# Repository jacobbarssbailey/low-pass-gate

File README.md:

# Dual low pass gate

This project provides tested plans for a 8HP Eurorack-format Dual Low Pass Gate.

## BOM

| Qty | Device | Value | Package | Parts | Notes |
| --- | ------ | ----- | ------- | ----- | ----- |
| 8 | Resistor | 1K | 0603 | R7, R11, R15, R24, R28, R32 | |
| 2 | Resistor | 4.7K | 0603 | R9, R27 | |
| 4 | Resistor | 47K | 0603 | R13, R17, R30, R34 | |
| 4 | Resistor | 10K | 0603 | R4, R14, R20, R31 | |
| 4 | Resistor | 100K | 0603 | R8, R16, R25, R33 | |
| 12 | Resistor | 200K | 0603 | R1, R2, R3, R5, R10, R12, R18, R19, R21, R22, R26, R29 | |
| 2 | Capacitor | 100p | 0603 | C3, C12 | |
| 2 | Capacitor | 560p | 0603 | C21, C22 | |
| 2 | Capacitor | 1.5n | 0603 | C4, C13 | |
| 8 | Capacitor | 100n | 0603 | C1, C5, C6, C8, C10, C15, C16, C19 | |
| 2 | Capacitor | 1µ | 0603 | C2, C11 | |
| 2 | Capacitor (Pol) | 47µ–100µ | Panasonic D | C14, C18 | |
| 4 | Pot | 100K | ALPS 9mm Vert | GAIN1, GAIN2, RMUTE1, RMUTE2 | |
| 10 | Audio Jack (Mono) |  | Inline | CTRL1, CTRL2, IN1, IN2, MUTE1, MUTE2, OUT1, OUT2, PLK1, PLK2 | [Erthenvar](https://erthenvar.myshopify.com/collections/accessories/products/3-5mm-inline-jacks) and others |
| 2 | Quad Op Amp | TL074 | SO14 | U1, U2 |  |
| 2 | Comparator | LM397 | SOT23-5 | IC2, IC5 |  |
| 8 | Schottky Diode |  | SOD323 | D1, D2, D3, D4, D5, D6, D7, D8 |  |
| 6 | Light Dependent Resistor | SR32-SR3 | VTL5C-SMALL | LDR1, LDR2, LDR3, LDR4, LDR5, LDR6 | [digikey.com](https://www.digikey.com/product-detail/en/advanced-photonix/NSL-32SR3/NSL-32SR3-ND/5039793) and others |
| 1 | 10 pin Power |  | 10 pin shrouded IDC 2.54mm pitch | P1 |  |
| 2 | LED[†](#leds) |  | 3mm | LED1, LED2 |  |

#### †LEDs
In the drive circuit, indicator LEDs and LDRs are driven in series, with identical current. For best results, use LEDs that have a acceptable brightness when driven in the range 0mA – 12mA.

### Assembly [important!]

The pairs of jacks IN1 & CTRL1 and IN2 & CTRL2 share a ground pin connection. Make sure to check CTRL1 and CTRL2 orientation before soldering.

## Operation and Controls

Each channel of the gate/filter is identical, save that Channel B's Audio Input is normalled to Channel A's.

 The control knob opens the filter and allows audio to pass. It attenuates the Control CV (normalled to =6V).

Pluck CV is a gate-to-trigger converter feeding the control circuit. Gate signals sent to this input will 'pluck' the control circuit, causing it to ring out.

 The mute input (normalled to =10V) will both shorten the response time of the filter, and apply a very mild hi-pass filter. In a musical sense, its effect on the filter is akin to softly holding a palm against a rung bell or plucked string.

 At very low values, near 0V the mute input will allow some audio to pass through the circuit without any control input. If this isn't desired, turn the mute knob up to 15-20%.

## Other notes

Increasing the capacitance of C21 and C22 will increase the resonance of the low pass filter. Quite strong filter resonance is achievable by changing this component value.

Other LDRs/Vactrols may work equally well. If test any and have particular recommendations, please open an issue here.

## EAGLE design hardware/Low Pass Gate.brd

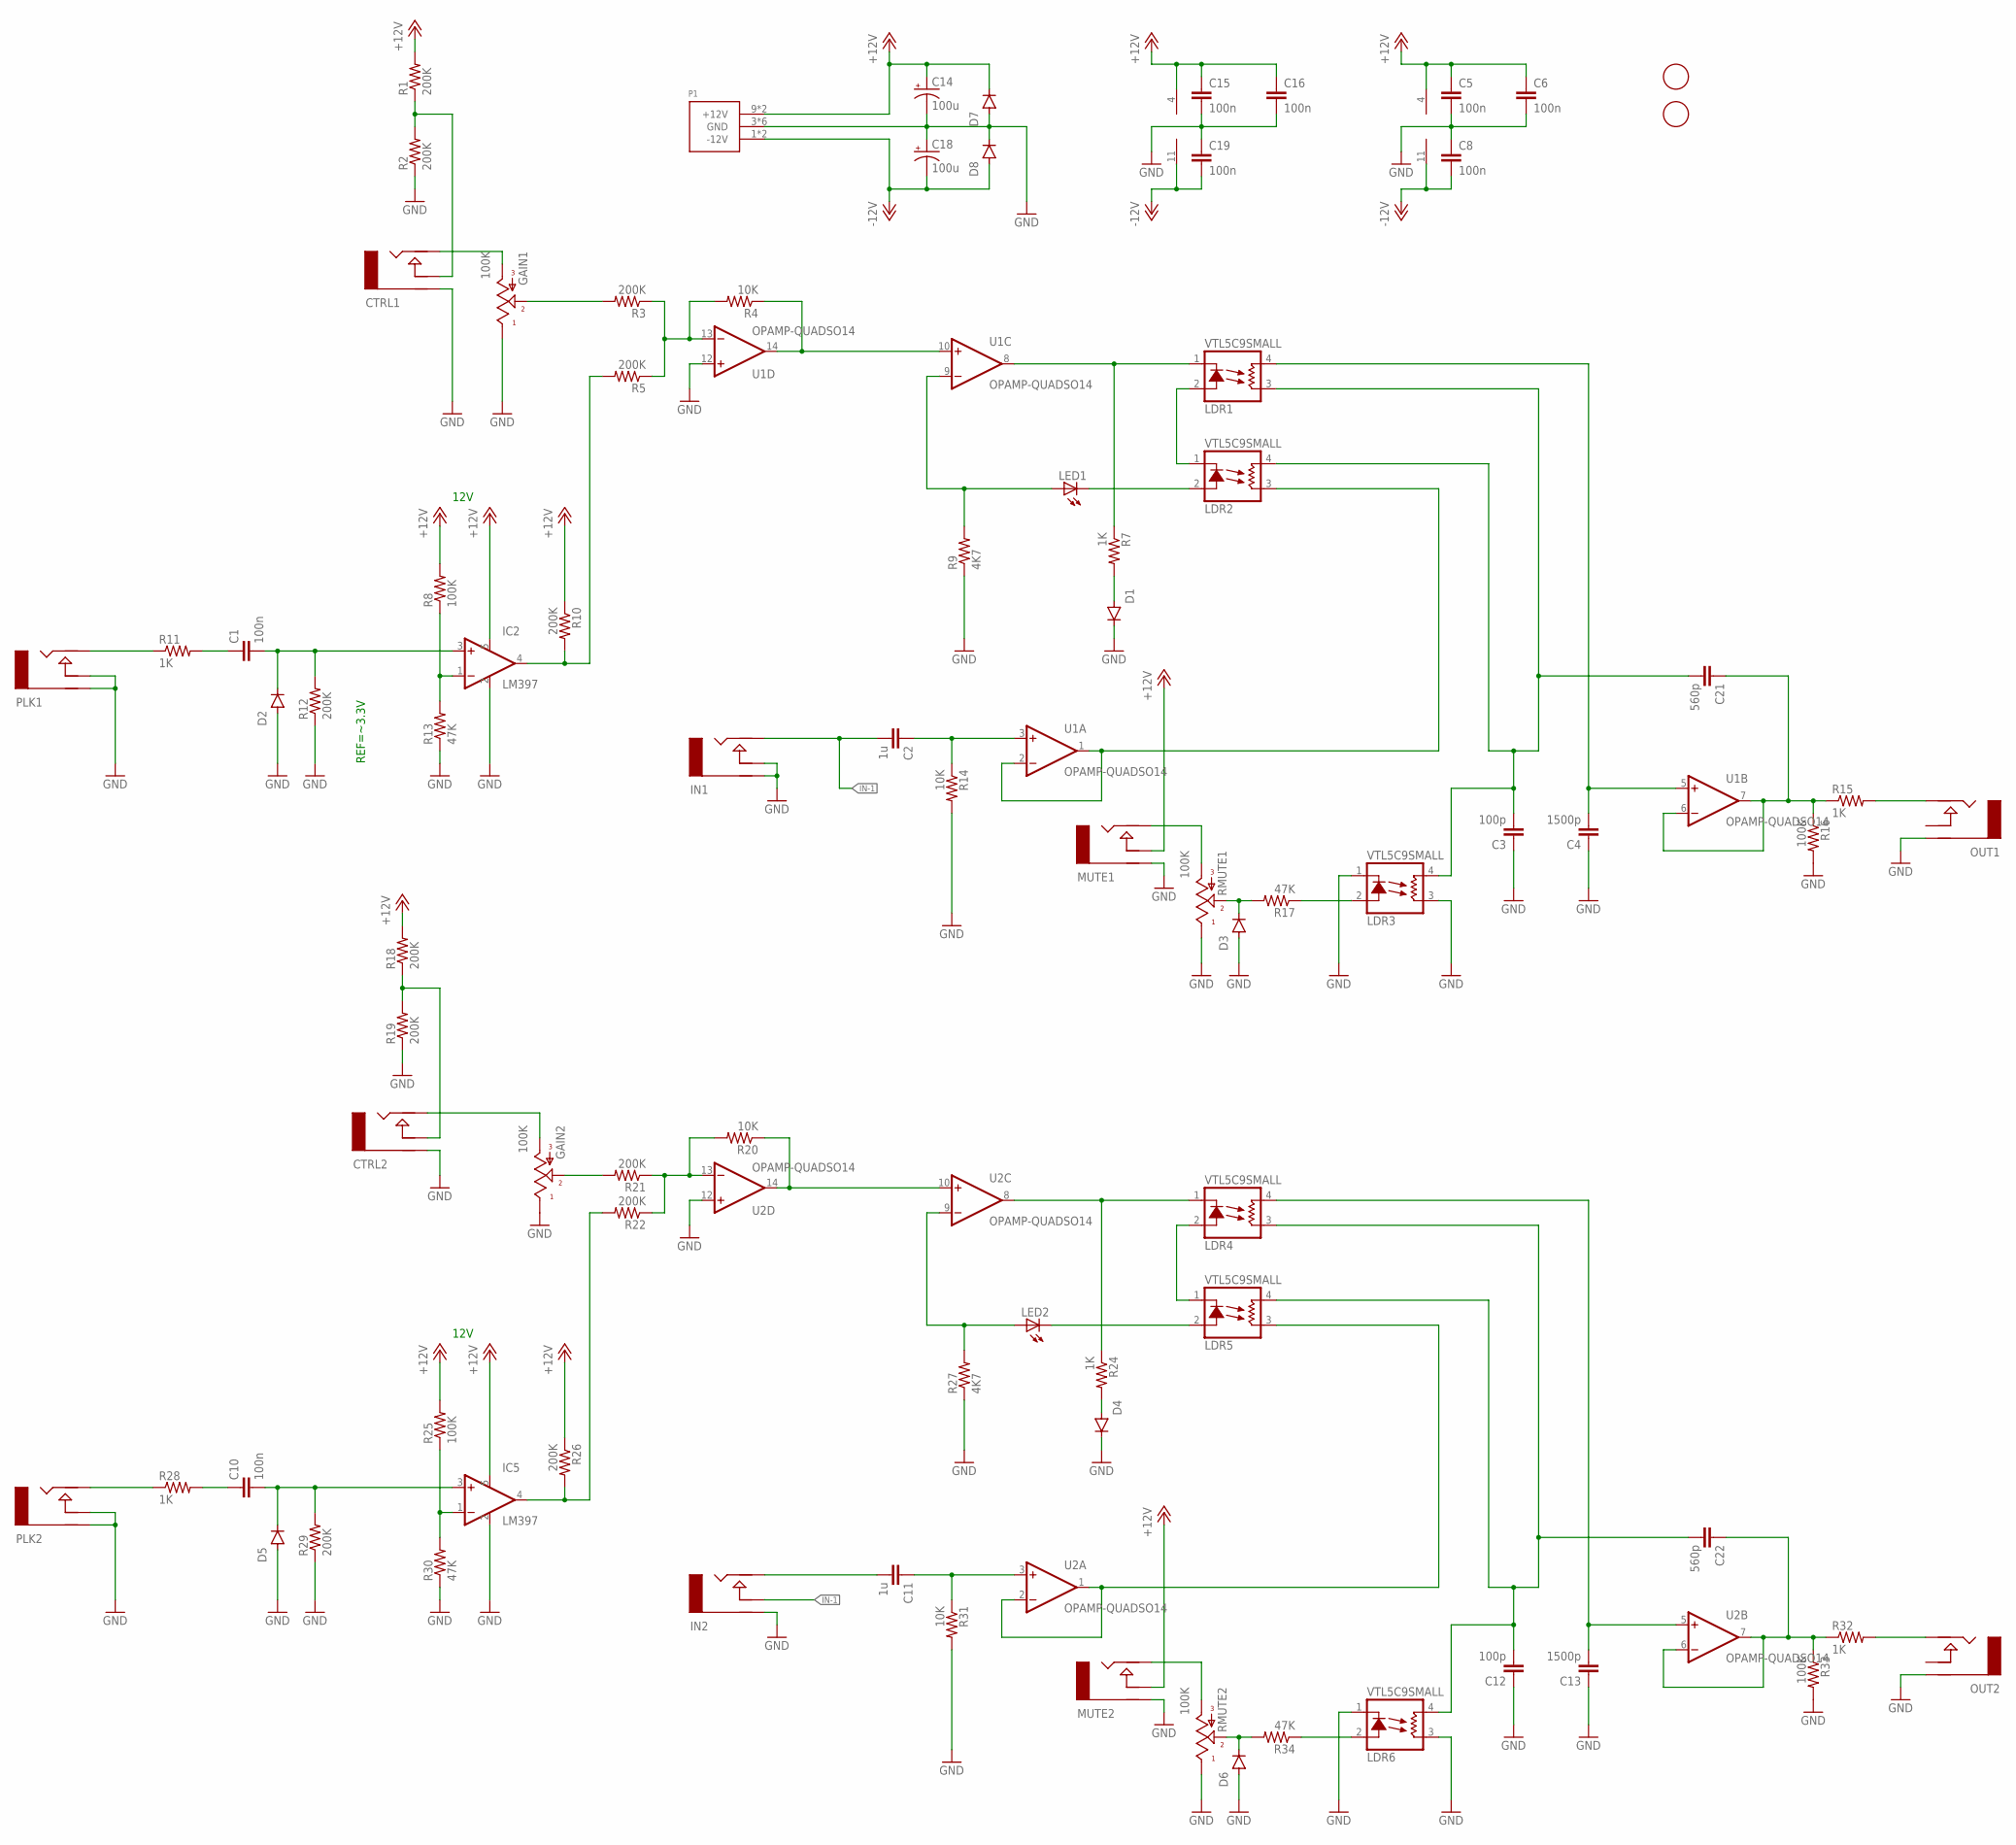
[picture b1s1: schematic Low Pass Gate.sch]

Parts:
C1, C5, C6, C8, C10, C15, C16, C19: 100n; 0805
C2, C11: 1u; 0805
C3, C12: 100p; 0805
C4, C13: 1500p; 0805
C14, C18: 100u; PANASONIC_D
C21, C22: 560p; 0805
CTRL1, CTRL2: AUDIO-JACKINLINE-FLOATGND; ERTHENVAR-JACK-INLINE-SHAREGND550
D1, D2, D3, D4, D5, D6, D7, D8: DIODE-SOD323-W; SOD323-W
GAIN1, GAIN2: 100K; ALPS_POT_KIT
IC2, IC5: LM397; SOT23-5
IN1, IN2: AUDIO-JACKINLINE-FLOATGND; ERTHENVAR-JACK-INLINE-SHAREGND550
LDR1, LDR2, LDR3, LDR4, LDR5, LDR6: VTL5C9SMALL; VTL5C-SMALL
LED1, LED2: LED3MM
MUTE1, MUTE2: AUDIO-JACKINLINE; ERTHENVAR-JACK-INLINE
OUT1, OUT2: AUDIO-JACKINLINE; ERTHENVAR-JACK-INLINE
P1: POWER_SIMPLE10_SHROUDED; POWER_10_SHROUDED
PLK1, PLK2: AUDIO-JACKINLINE; ERTHENVAR-JACK-INLINE
R1, R2, R3, R5, R10, R12, R18, R19, R21, R22, R26, R29: 200K; 0603-RES
R4, R14, R20, R31: 10K; 0603-RES
R7, R11, R15, R24, R28, R32: 1K; 0603-RES
R8, R16, R25, R33: 100K; 0603-RES
R9, R27: 4K7; 0603-RES
R13, R17, R30, R34: 47K; 0603-RES
RMUTE1, RMUTE2: 100K; ALPS_POT_KIT
U1, U2: OPAMP-QUADSO14; SO14
U$1, U$2: FIDUCIAL; FIDUCIAL_1MM

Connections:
+12V: C5.1, C6.1, C14.+, C15.1, C16.1, D7.C, IC2.5 (V+), IC5.5 (V+), MUTE1.N (NORM), MUTE2.N (NORM), P1.9 (+12V), P1.10 (+12V), R1.2, R8.2, R10.1, R18.2, R25.2, R26.1, U1.4 (VCC), U2.4 (VCC)
-12V: C8.2, C18.-, C19.2, D8.A, P1.1 (-12V), P1.2 (-12V), U1.11 (VEE), U2.11 (VEE)
GND: C3.1, C4.1, C5.2, C6.2, C8.1, C12.1, C13.1, C14.-, C15.2, C16.2, C18.+, C19.1, CTRL1.G (RING), CTRL2.G (RING), D1.C, D2.A, D3.A, D4.C, D5.A, D6.A, D7.A, D8.C, GAIN1.P$1 (E), GAIN2.P$1 (E), IC2.2 (GND), IC5.2 (GND), IN1.G (RING), IN1.N (NORM), IN2.G (RING), LDR3.1 (C), LDR3.3 (L1), LDR6.1 (C), LDR6.3 (L1), MUTE1.G (RING), MUTE2.G (RING), OUT1.G (RING), OUT2.G (RING), P1.3 (GND), P1.4 (GND), P1.5 (GND), P1.6 (GND), P1.7 (GND), P1.8 (GND), PLK1.G (RING), PLK1.N (NORM), PLK2.G (RING), PLK2.N (NORM), R2.1, R9.1, R12.1, R13.1, R14.2, R16.2, R19.1, R27.1, R29.1, R30.1, R31.2, R33.2, RMUTE1.P$1 (E), RMUTE2.P$1 (E), U1.12 (+IN), U2.12 (+IN)
IN-1: C2.2, IN1.T (TIP), IN2.N (NORM)
unnamed: R20.2, R21.1, R22.1, U2.13 (-IN)
unnamed: LDR4.1 (C), R24.1, U2.8 (OUT)
unnamed: LDR4.2 (A), LDR5.1 (C)
unnamed: GAIN2.P$2 (S), R21.2
unnamed: LED2.A, R27.2, U2.9 (-IN)
unnamed: LDR5.2 (A), LED2.K (C)
unnamed: CTRL2.N (NORM), R18.1, R19.2
unnamed: CTRL1.T (TIP), GAIN1.P$3 (A)
unnamed: D4.A, R24.2
unnamed: CTRL2.T (TIP), GAIN2.P$3 (A)
unnamed: PLK2.T (TIP), R28.1
unnamed: C11.2, IN2.T (TIP)
unnamed: IC5.4 (OUT), R22.2, R26.2
unnamed: C10.2, D5.C, IC5.3 (+IN), R29.2
unnamed: C10.1, R28.2
unnamed: IC5.1 (-IN), R25.1, R30.2
unnamed: R3.1, R4.2, R5.1, U1.13 (-IN)
unnamed: CTRL1.N (NORM), R1.1, R2.2
unnamed: IC2.4 (OUT), R5.2, R10.2
unnamed: D6.C, R34.2, RMUTE2.P$2 (S)
unnamed: OUT2.T (TIP), R32.2
unnamed: C11.1, R31.1, U2.3 (+IN)
unnamed: C13.2, LDR4.4 (L2), U2.5 (+IN)
unnamed: C1.2, D2.C, IC2.3 (+IN), R12.2
unnamed: LDR5.3 (L1), U2.1 (OUT), U2.2 (-IN)
unnamed: C22.1, R32.1, R33.1, U2.6 (-IN), U2.7 (OUT)
unnamed: C1.1, R11.2
unnamed: LDR6.2 (A), R34.1
unnamed: C12.2, C22.2, LDR4.3 (L1), LDR5.4 (L2), LDR6.4 (L2)
unnamed: IC2.1 (-IN), R8.1, R13.2
unnamed: PLK1.T (TIP), R11.1
unnamed: MUTE2.T (TIP), RMUTE2.P$3 (A)
unnamed: D1.A, R7.2
unnamed: OUT1.T (TIP), R15.2
unnamed: C2.1, R14.1, U1.3 (+IN)
unnamed: C4.2, LDR1.4 (L2), U1.5 (+IN)
unnamed: LDR2.3 (L1), U1.1 (OUT), U1.2 (-IN)
unnamed: C21.1, R15.1, R16.1, U1.6 (-IN), U1.7 (OUT)
unnamed: C3.2, C21.2, LDR1.3 (L1), LDR2.4 (L2), LDR3.4 (L2)
unnamed: MUTE1.T (TIP), RMUTE1.P$3 (A)
unnamed: LDR3.2 (A), R17.1
unnamed: LDR2.2 (A), LED1.K (C)
unnamed: LDR1.1 (C), R7.1, U1.8 (OUT)
unnamed: LDR1.2 (A), LDR2.1 (C)
unnamed: D3.C, R17.2, RMUTE1.P$2 (S)
unnamed: GAIN1.P$2 (S), R3.2
unnamed: LED1.A, R9.2, U1.9 (-IN)
VSIG: R20.1, U2.10 (+IN), U2.14 (OUT)
VSIG1: R4.1, U1.10 (+IN), U1.14 (OUT)

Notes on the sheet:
12V
REF=~3.3V

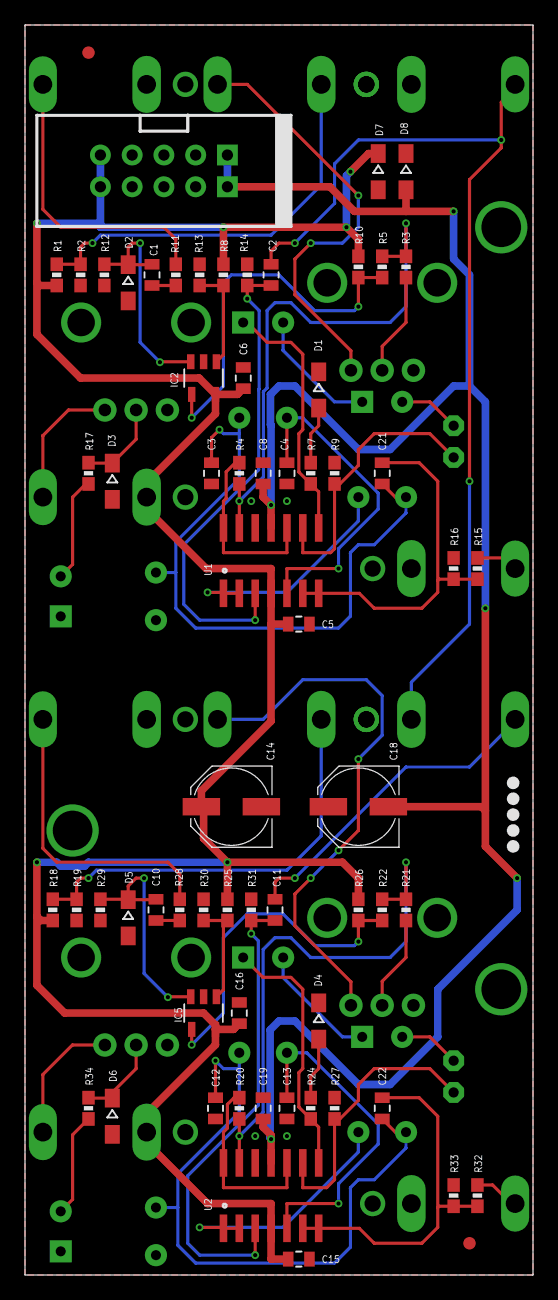
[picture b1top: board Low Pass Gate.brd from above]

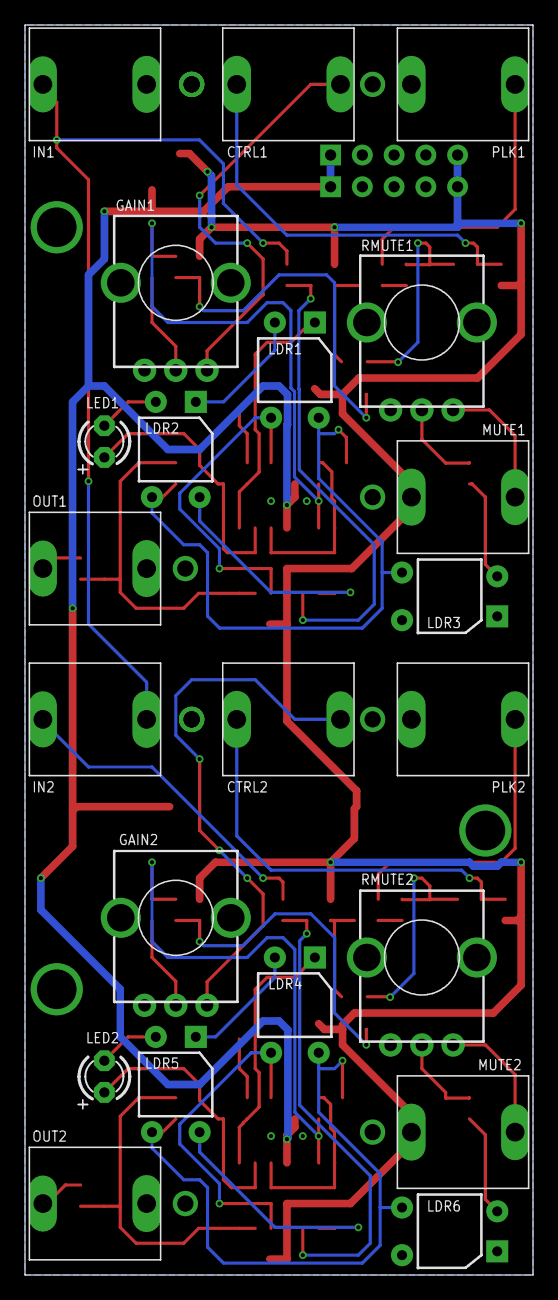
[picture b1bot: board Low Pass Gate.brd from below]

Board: 2 copper layers, 40.6 x 100.0 mm, 87 parts (22 on the bottom side), 53 nets.

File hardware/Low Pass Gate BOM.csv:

"Qty";"Value";"Device";"Package";"Parts";"Description";"MF";"MPN";"OC_FARNELL";"OC_NEWARK";"PROD_ID";
"8";"";"DIODE-SOD323-W";"SOD323-W";"D1, D2, D3, D4, D5, D6, D7, D8";"DIODE";"";"";"";"";"";
"2";"";"LED3MM";"LED3MM";"LED1, LED2";"LED";"";"";"";"";"";
"4";"100K";"POTALPS-KIT";"ALPS_POT_KIT";"GAIN1, GAIN2, RMUTE1, RMUTE2";"";"";"";"";"";"RES-09177";
"4";"100K";"RESISTOR0603-RES";"0603-RES";"R8, R16, R25, R33";"Resistor";"";"";"";"";"";
"8";"100n";"CAP0805";"0805";"C1, C5, C6, C8, C10, C15, C16, C19";"Capacitor";"";"";"";"";"";
"4";"100p";"CAP0805";"0805";"C3, C4, C12, C13";"Capacitor";"";"";"";"";"";
"2";"100u";"CAP_POLD";"PANASONIC_D";"C14, C18";"Capacitor Polarized";"";"";"";"";"";
"4";"10K";"RESISTOR0603-RES";"0603-RES";"R4, R14, R20, R31";"Resistor";"";"";"";"";"";
"8";"1K";"RESISTOR0603-RES";"0603-RES";"R7, R9, R11, R15, R24, R27, R28, R32";"Resistor";"";"";"";"";"";
"2";"1u";"CAP0805";"0805";"C2, C11";"Capacitor";"";"";"";"";"";
"12";"200K";"RESISTOR0603-RES";"0603-RES";"R1, R2, R3, R5, R10, R12, R18, R19, R21, R22, R26, R29";"Resistor";"";"";"";"";"";
"4";"47K";"RESISTOR0603-RES";"0603-RES";"R13, R17, R30, R34";"Resistor";"";"";"";"";"";
"2";"560p";"CAP0805";"0805";"C21, C22";"Capacitor";"";"";"";"";"";
"6";"AUDIO-JACKINLINE";"AUDIO-JACKINLINE";"ERTHENVAR-JACK-INLINE";"MUTE1, MUTE2, OUT1, OUT2, PLK1, PLK2";"Switching Mono 3.5mm Audio Jack from Erthenvar. Horizontal package.";"";"";"";"";"";
"4";"AUDIO-JACKINLINE-FLOATGND";"AUDIO-JACKINLINE-FLOATGND";"ERTHENVAR-JACK-INLINE-SHAREGND550";"CTRL1, CTRL2, IN1, IN2";"Switching Mono 3.5mm Audio Jack from Erthenvar. Horizontal package.";"";"";"";"";"";
"2";"FIDUCIAL";"FIDUCIAL";"FIDUCIAL_1MM";"U$1, U$2";"For use by pick and place machines to calibrate the vision/machine, 1mm";"";"";"";"";"";
"2";"LM397";"LM397";"SOT23-5";"IC2, IC5";"7 Single General-Purpose Voltage Comparator";"";"";"";"";"";
"2";"OPAMP-QUADSO14";"OPAMP-QUADSO14";"SO14";"U1, U2";"";"";"";"";"";"";
"1";"POWER_SIMPLE10_SHROUDED";"POWER_SIMPLE10_SHROUDED";"POWER_10_SHROUDED";"P1";"";"";"";"";"";"";
"6";"VTL5C9SMALL";"VTL5C9SMALL";"VTL5C-SMALL";"LDR1, LDR2, LDR3, LDR4, LDR5, LDR6";"Low Cost Axial Vactrols";"VACTEC PHOTO";"VTL5C9";"2067857";"95F9033";"";

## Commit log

2019-06-21 init
2019-06-21 remove lck
2019-06-21 git ignore
2019-06-23 add test fixture alignment holes
2019-06-24 use throughhole bulk caps
2019-06-24 hide private files
2019-06-24 fix power connector location for keyed connector width
2019-07-09 revert to using ldr muting circuit
2019-07-28 update to rev E
2019-07-29 updated BOM for rev E
2019-07-29 remove gitignore
2019-07-29 .gitignore fix
2019-07-29 hardware cleanup
2019-07-31 media diagrams, pdfs, clean up schm
2019-07-31 fix link
2019-09-17 update docs to mention audio pass through at low mute voltages
2019-09-18 fix C4/C13 value (that was resulting in 5.6x f(c) in filter)
2019-09-19 Additional fix for C4/C13 value causing audio bleedthrough at low mute settings
2019-09-25 adjust led drive current resistor
2019-10-25 fix drive resistor value

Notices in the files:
parts and their libraries:
SparkFun-Passives: Licensing: Creative Commons ShareAlike 4.0 International - https://creativecommons.org/licenses/by-sa/4.0
